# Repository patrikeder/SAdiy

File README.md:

# SAdiy: DIY swept spectrum analyzer

A swept low-IF spectrum analyzer built from ready-made RF modules and controlled by a BeagleBone Black (BBB). The software runs on a PC today against a simulated RF chain. It has not run on the real hardware yet: see [Status](#status).

The code is Python. C++ or Rust comes in only if a measured time per point demands it (`native/`).

## Signal chain

Planned:

```
RF in -> DC block/ESD -> PE4302 -> 500 MHz LPF -> 30 dB amp -> AD831 mixer -> 10.7 MHz IF filter -> IF amp -> log detector -> ADS1115 -> BBB
                                                                  ^
ADF4351 (LO = RF + 10.7 MHz) -> LPF + pad -----------------------+
```

Built so far: PE4302, amp, AD831, detector and ADF4351. The missing stages are listed in priority order in [hw/todo-parts.md](hw/todo-parts.md).

- **Range:** 30 to 480 MHz by default (`config/default.toml`). The AD831 LO limit puts the ceiling at about 489 MHz.
- **Image:** the low IF puts an image 21.4 MHz above each RF, so every signal also shows a copy 21.4 MHz lower on the sweep axis. The optional **Image reject** setting (two sweeps per trace with the LO on both sides, lower reading kept) removes it above about 45 MHz at twice the sweep time; tested in the simulator only.
- **ADC:** an ADS1115 on I2C reads the detector. The BBB on-chip AIN0 stays wired as an optional cross-check.

## Quick start (PC, no hardware)

```bash
python3 -m venv .venv && . .venv/bin/activate
pip install -e .[dev,ui]      # ui adds PyQtGraph and PyQt5, only needed for the GUI
pytest
```

On a Raspberry Pi (aarch64) PyPI has no PyQt5 wheel, so use the Debian packages and a venv that can see them:

```bash
sudo apt install python3-pyqt5 python3-pyqtgraph python3-zmq python3-numpy    # python3-pyqt6 works too
python3 -m venv --system-site-packages .venv && . .venv/bin/activate
pip install -e . --no-deps
```

Run the spectrum analyzer GUI. It starts its own simulated hardware, and its Pins tab drives a fake board:

```bash
python -m sadiy.ui.sa_gui --sim
```

Or run the daemon and a terminal client separately:

```bash
python -m sadiy.server.sweepd --sim &      # publishes on tcp 5556, takes commands on tcp 5557
python -m sadiy.ui.cli_client --count 5    # prints the peak of each sweep
python -m sadiy.ui.cli_client --log-level warning   # also what sweepd reports: its history, then live
```

Bring-up helpers that need no hardware:

```bash
python tools/bringup.py pe4302-pattern --db 16 --from-db 15.5   # V1..V6 write order, for a logic analyzer
python tools/bringup.py pll --mhz 110.7                         # divider, INT, FRAC, MOD
```

Run from a project checkout: the config is read from `config/default.toml` next to `src/`.

## On the BBB

Setup is in [deploy/bbb-setup.md](deploy/bbb-setup.md), including first install and updates without internet: `python tools/make_bbb_package.py` builds the package in `dist/`, and `deploy/sadiy-update.sh` updates an existing installation from it. Sweeping on real hardware is not written yet, so for now the daemon runs in bench mode only:

```bash
cd /opt/sadiy && sudo PYTHONPATH=src python3 -m sadiy.server.sweepd --bench-only --config /etc/sadiy/local.toml   # on the BBB
python -m sadiy.ui.sa_gui --host <bbb-ip> --connect   # on the PC
```

The GUI's **Pins** tab then gives wiring tests over the network:

- a clickable drawing of P8 and P9 with the boards, and live pin levels
- raw access to the ADF4351, PE4302 and both ADCs
- check patterns with a preview and CSV export, to compare with a logic analyzer capture

The daemon enforces the safety rules: the attenuator starts at 31.5 dB, RF outputs stay off until the PLL is locked, and all lines return to a safe state if the client disappears. See [docs/gui.md](docs/gui.md).

**Messages from the daemon.** `sweepd` logs at five levels. The default (info) goes to stderr, which is the journal under systemd: `journalctl -u sweepd -f` over ssh. `-v` is debug, `-vv` adds trace (every point and SPI word, ssh only), `-q` is warning; `[log] level` in the config does the same. Errors, warnings, info and debug also reach the GUI, in the Device log on the Advanced tab, with a count of unread problems on the tab. See "Logging" in [docs/architecture.md](docs/architecture.md).

## How it fits together

```
 sweepd (one process, on the BBB)               clients (any number, any host)
 +-----------------------------------+          +---------------------------+
 | sweep engine or bench mode        |   PUB    | sa_gui / cli_client       |
 | lock detect, median, flags, cal   | -------> |  sweeps: dBm + flags      |
 | PE4302 (GPIO) ADF4351 (SPI)       |          |  log: errors, warnings    |
 | ADS1115 (I2C) AIN0 (IIO)          |   REP    | plot, markers, Pins,      |
 | log ring                          | <------- | Device log                |
 +-----------------------------------+          | commands (JSON)           |
        +--> stderr / journald (ssh)             +---------------------------+
```

`sweepd` is the only process that touches the hardware. Clients talk to it over ZeroMQ: sweep frames and log records on port 5556, JSON commands on port 5557. The BBB does the per-point work (lock detect, median of the reads, calibration, flags for points it does not trust); the GUI keeps the trace modes, markers and peak search. Code layers as `hal` -> `drivers` -> `core` -> `server` -> `ui`, and only `hal` touches the OS, so everything above it runs on a PC against fakes and the simulator. Details and the design decisions are in [docs/architecture.md](docs/architecture.md).

## Repository layout

| Path | What |
|---|---|
| `src/sadiy/pinmap.py` | the BBB pin map: nets, GPIO numbers, what each pin may do. Read by the diagram generator, the daemon and the GUI |
| `src/sadiy/hal/` | SPI, GPIO, I2C and ADC abstraction: Linux backends and recording fakes |
| `src/sadiy/drivers/` | PE4302, ADF4351, ADS1115 and on-chip ADC drivers |
| `src/sadiy/core/` | frequency plan, detector model, calibration, sweep engine with lock gating, median and flags (no hardware access) |
| `src/sadiy/server/` | `sweepd` daemon, wire protocol, bench mode |
| `src/sadiy/logs.py` | log levels, the numbered ring buffer the GUI fetches from, repeat folding; standard library only |
| `src/sadiy/ui/` | terminal client and GUI (`sa_gui.py`, `bench_tab.py`); logic without Qt is in `sa_core.py`, `bench_core.py` and `log_core.py`. `qt_client.py` is an old skeleton |
| `src/sadiy/sim.py` | simulated RF chain |
| `src/sadiy/patterns.py` | pin patterns and SPI frames, for logic analyzer comparison |
| `config/` | TOML configuration; values marked VERIFY need checking on the real boards |
| `hw/` | wiring, diagrams, netlist, per-board notes, test points, missing parts, adapter board (KiCad) |
| `docs/` | architecture, bring-up plans, GUI manual, `handoff.md` (starting on another PC) |
| `deploy/` | BBB setup notes, systemd units, install, update and pin mode scripts, example local config |
| `sna/` | second project: a scalar network analyzer reusing the same chain |
| `tools/` | bring-up and calibration helpers, `gen_diagrams.py`, `make_bbb_package.py` |
| `dist/` | BBB packages built by `make_bbb_package.py`; not in git |
| `tests/` | pytest suite, runs on a PC; GUI tests run offscreen and are skipped without the GUI packages |
| `native/` | placeholder for C++ or Rust |

`hw/netlist.md` and `hw/diagrams/` are generated. To change them, edit `src/sadiy/pinmap.py` or `tools/gen_diagrams.py` and run `python tools/gen_diagrams.py`.

## Hardware documentation

| Document | What |
|---|---|
| [hw/wiring-bbb.md](hw/wiring-bbb.md) | BBB wiring, wiring order, power-on checks |
| [hw/netlist.md](hw/netlist.md) | every signal, strap and supply pin |
| [hw/boards/sbc-adapter/README.md](hw/boards/sbc-adapter/README.md) | adapter board that carries the modules on the BBB |
| [hw/as-built.md](hw/as-built.md) | what is really on the bench |
| [docs/bringup.md](docs/bringup.md) | staged bring-up plan with pass criteria |

The adapter board is BBB only: its Raspberry Pi connector was removed. The Raspberry Pi wiring notes and software paths are still in the repo but are no longer developed.

## Status

| Part | State |
|---|---|
| Frequency plan and PLL math, detector model, calibration, auto-ranging | done, tested |
| Sweep engine, `sweepd`, protocol, terminal client, simulator | done, tested against the simulator |
| Per-point lock gating, median of the reads, flags (unlocked, overload, at floor, outlier) | done, tested with fakes and the simulator; thresholds (`max_dbm`, `floor_dbm`, `outlier_db`) not yet checked on the real detector, and the lock line is not read from a real GPIO until `build_hw_engine` exists |
| Image rejection (two sweeps, opposite LO side, lower reading kept) | done, tested against the simulator; the real mixer with a low-side LO is not verified |
| Logging on the BBB (levels, journald, ring, `log` command) and the GUI Device log | done, tested; never run on a real BBB |
| Spectrum analyzer GUI | done, smoke-tested offscreen against the simulator; not yet used with real hardware or on a real display |
| PE4302 driver | done, tested with fakes; weights and polarity not yet confirmed on the module (`pe4302-walk`) |
| ADS1115 driver | done, tested against a register model only; sweeps do not use it yet |
| Bench mode (Pins tab) | done, **tested on the fake backend only**; the Linux backend has never run on a BBB |
| ADF4351 register packing | R0..R5 written and unit-tested for field positions; **not yet checked against the datasheet text or ADI's software** |
| Sweeping on real hardware (`build_hw_engine`) | **not written** |
| GPIO backend | sysfs; moves to libgpiod once the image is fixed |

Unverified on a real BBB: the pin map, pin multiplexing and `config-pin` modes, and the SPI and I2C device numbers.

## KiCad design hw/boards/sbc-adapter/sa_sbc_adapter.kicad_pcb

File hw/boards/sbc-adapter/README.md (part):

# SBC adapter (KiCad project)

One board that lets the **BeagleBone Black** reach the module boards (PE4302, ADF4351, detector, ADS1115). The board sits on the BBB like a cape: P8 and P9 are male pin headers on the **bottom** side, everything else (module headers, jumpers, test points) is on the **top** side.

**Raspberry Pi support was removed (2026-11-01)** to keep the board to one SBC: J3 (2x20 IDC), the 13 RPi-side series resistors (R2, R4 .. R26) and the RPi supply jumpers JP2 / JP4 are gone from the schematic and the board. Every BBB signal keeps its 220 ohm series resistor at the BBB header (R1, R3 .. R25), as source termination and fault-current limit.

The pin map comes from `../../netlist.md` and `../../wiring-bbb.md`. Nothing was remapped.

## Files

| File | Content |
|---|---|
| `sa_sbc_adapter.kicad_sch` | schematic (single sheet, A1), KiCad 8 file format |
| `sa_sbc_adapter.kicad_pro` | minimal project file |
| `sadiy.kicad_sym`, `sym-lib-table` | project symbol library (all symbols are custom, footprints are stock KiCad ones) |
| `gen_schematic.py` | generator of the FIRST (two-SBC) schematic, a record only: **do not run it over the `.kicad_sch`** |
| `check_schematic.py` | standalone connectivity check against the pin map (no KiCad needed) |
| `preview.svg`, `preview.png` | schematic preview drawn by the generator, **not a KiCad render** |
| `sa_sbc_adapter.kicad_pcb` | board, connectors placed to the BBB cape geometry (see "Board placement") |
| `sadiy.pretty/`, `fp-lib-table` | project footprint library: `BBB_Header_2x23_Male_Bottom` |
| `gen_footprints.py` | writes `sadiy.pretty/` and `fp-lib-table` |
| `remove_rpi.py` | removes J3, JP2, JP4 and the RPi-side resistors from the schematic and the board (record of the 2026-11-01 edit, not re-runnable) |
| `route_check.py`, `route_report.py`, `ROUTABILITY.md`, `routability/` | routability feasibility check (see `ROUTABILITY.md`) |
| `place_connectors.py` | (first layout, includes J3) puts J1, J2, J3 and the cape outline / keep-outs (`Dwgs.User`) on the board (re-runnable) |
| `align_components.py` | (first layout, before the hand edits and before J3 was removed) **places every other part on a regular lattice** (rows, columns, one orientation per class), fits the board outline to the parts and writes it on `Edge.Cuts`; deterministic, re-runnable. Run it after `place_connectors.py` |
| `place_components.py` | earlier free-form placement (greedy, net-driven) that was used to find the macro layout; superseded by `align_components.py`, kept for experiments |
| `check_components.py` | (needs J3, so it no longer runs on the current board) checks overlaps, the board outline, the alignment (lattice, orientations, rows) and the signal-integrity distances |
| `check_placement.py` | (needs J3) checks the pad positions in the board file against the cape geometry |
| `placement.svg`, `placement.png` | placement preview of ALL parts, drawn from the placement data (pads, courtyards, ratsnest of the signal nets), **not a KiCad render** |

The `.kicad_pcb` and `.kicad_sch` are yours. KiCad 10 re-saved them and the board has hand-placed parts (test points, some resistors, JP2/JP4/JP6 before they were removed or moved), so none of the placement scripts is re-run any more.

## Status

- The schematic was checked without KiCad: nets built from wires, labels and pin positions. After the RPi removal: every remaining pin keeps its net, no wire end dangles, no RPI_* label is left.
- **Not yet checked in KiCad.** Run ERC and DRC and pass the output back. Then use "Update PCB from Schematic" once to confirm that schematic and board agree (they were edited in the same way).

## Signal map

| Net | BBB | Module |
|---|---|---|
| SYN_CLK | P9.22 | J6 pin 7 (ADF4351 CLK) |
| SYN_DATA | P9.18 | J6 pin 6 (DAT) |
| SYN_LE | P9.17 | J6 pin 5 (LE) |
| SYN_LD | P9.23 | J6 pin 9 (LD), SBC input |
| SYN_CE | P9.27 | J12 pin 3, jumper to J6 pin 3 (CE) |
| ATT_V1..V6 | P8.7, 8, 9, 10, 11, 12 | J4 pins 2..7 (PE4302 V1..V6) |
| I2C_SDA / I2C_SCL | P9.20 / P9.19 (I2C2) | J10 pins 4 / 3 (ADS1115) |
| detector | P9.39 AIN0, P9.34 GNDA_ADC, P9.32 VDD_ADC (clamp only) | divider from J8 |

## Jumpers and options

| Part | Setting |
|---|---|
| JP1 | 5 V rail joins the BBB VDD_5V (P9.5/6). Case A: external 5 V on J11 powers the BBB, fit JP1 and do not plug the BBB's own supply. Case B: the BBB powers the modules, fit JP1 and leave J11 empty. A BBB powered over USB only has no VDD_5V. |
| JP3 | 3.3 V rail from the BBB (P9.3/4). |
| J12 | ADF4351 CE: jumper 1-2 = tied high (default), 2-3 = from the SBC pin. |
| JP5 | ADF4351 PDR tied high. Remove if the board already pulls it up. |
| JP6 | BBB analog path (divider to AIN0). |
| R27..R32 | 2.2k pull-ups on V1..V6, default after boot = 31.5 dB. Remove for 0 dB. |
| R38 (0R) | joins AGND to GND at one point. |
| 4.7k on I2C | not fitted (DNP). The BBB I2C2 already has pull-ups. |

## Parts (from the schematic)

25 resistors (13 x 220R series, 6 x 2.2k, 2 x 1k, 1 x 3.01k, 1 x 0R, 2 x 4.7k DNP), 10 capacitors (4 x 10u 0805, 6 x 100n 0603), 3 ferrite beads (0805, 2 A), 1 resettable fuse (1812, 2 A), 2 x BAT54S (SOT-23), 11 connectors, 4 jumper headers, 23 test points named as in `../../test-points.md` (TP_5V, TP_5V_SYN, TP_3V3_ATT, TP_PE_V1..V6, TP_SYN_*, TP_DET_OUT, TP_ADC_IN, plus grounds and rails). Footprints are assigned, using stock KiCad libraries.

## Decisions that go beyond the repo notes

- 220 ohm series resistors at the BBB header on every signal (source termination). With the 2.2k pull-ups the low level at the PE4302 input is about 0.3 V, well under its threshold.
- BBB divider is 1k over 3.01k (ratio 0.751, 1.9 V in gives about 1.43 V), 100 nF at the tap, BAT54S clamp to GNDA_ADC and VDD_ADC. Put `detector.divider_ratio = 0.751` in `config/default.toml`.
- ADS1115 path: 1k, 100 nF and a BAT54S clamp to 3V3 and ground. The ADS1115 is a **breakout header** (VDD GND SCL SDA ADDR ALRT A0 A1 A2 A3), not a chip on the board.
- The BBB I2C2 drives I2C_SDA / I2C_SCL for the ADS1115.
- Ferrite beads between the BBB rails and the ADF4351 5 V, the detector 5 V and the PE4302 3.3 V.

## Board placement

Cape geometry (BeagleBone cape, from the SparkFun `BEAGLE_BONE_BLACK_CAPE` footprint, which was made from the BBB gerbers), seen from the top, origin at the top-left corner of the 86.36 x 54.61 mm cape outline. The outline is drawn on `Dwgs.User` at (170, 40) on the board, to the right of the other parts. It is a reference, not the board edge.

| | pin 1 | rows |
|---|---|---|
| P8 (J2) | x = 20.32 mm, y = 4.445 mm | odd pins y = 4.445, even pins y = 1.905 (outer row, top edge) |
| P9 (J1) | x = 20.32 mm, y = 52.705 mm | odd pins y = 52.705 (outer row, bottom edge), even pins y = 50.165 |

Both headers: pin 1 at the Ethernet (left) end, 23 pins per row, 2.54 mm pitch, even pins above odd pins. The two headers are 48.26 mm apart.

- **J1, J2** are on the bottom side with the custom footprint `sadiy:BBB_Header_2x23_Male_Bottom`. The stock 2x23 header cannot be used there: KiCad mirrors a footprint when it moves to the bottom, which gives the wrong pad pattern for P8/P9. The custom footprint is the mirror image, so after KiCad flips it the pads sit exactly on the BBB pattern. Pin 1 is the footprint origin; keep the orientation at 0 and the side at B.Cu. It has no 3D model.
- Also drawn on `Dwgs.User`: the Ethernet connector keep-out, the top-left cut and the three rounded corners of the cape (from the same SparkFun footprint). The reference outline is only for orientation: the board is larger than the cape (see "Component placement"). Not placed: the four BBB mounting holes.
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
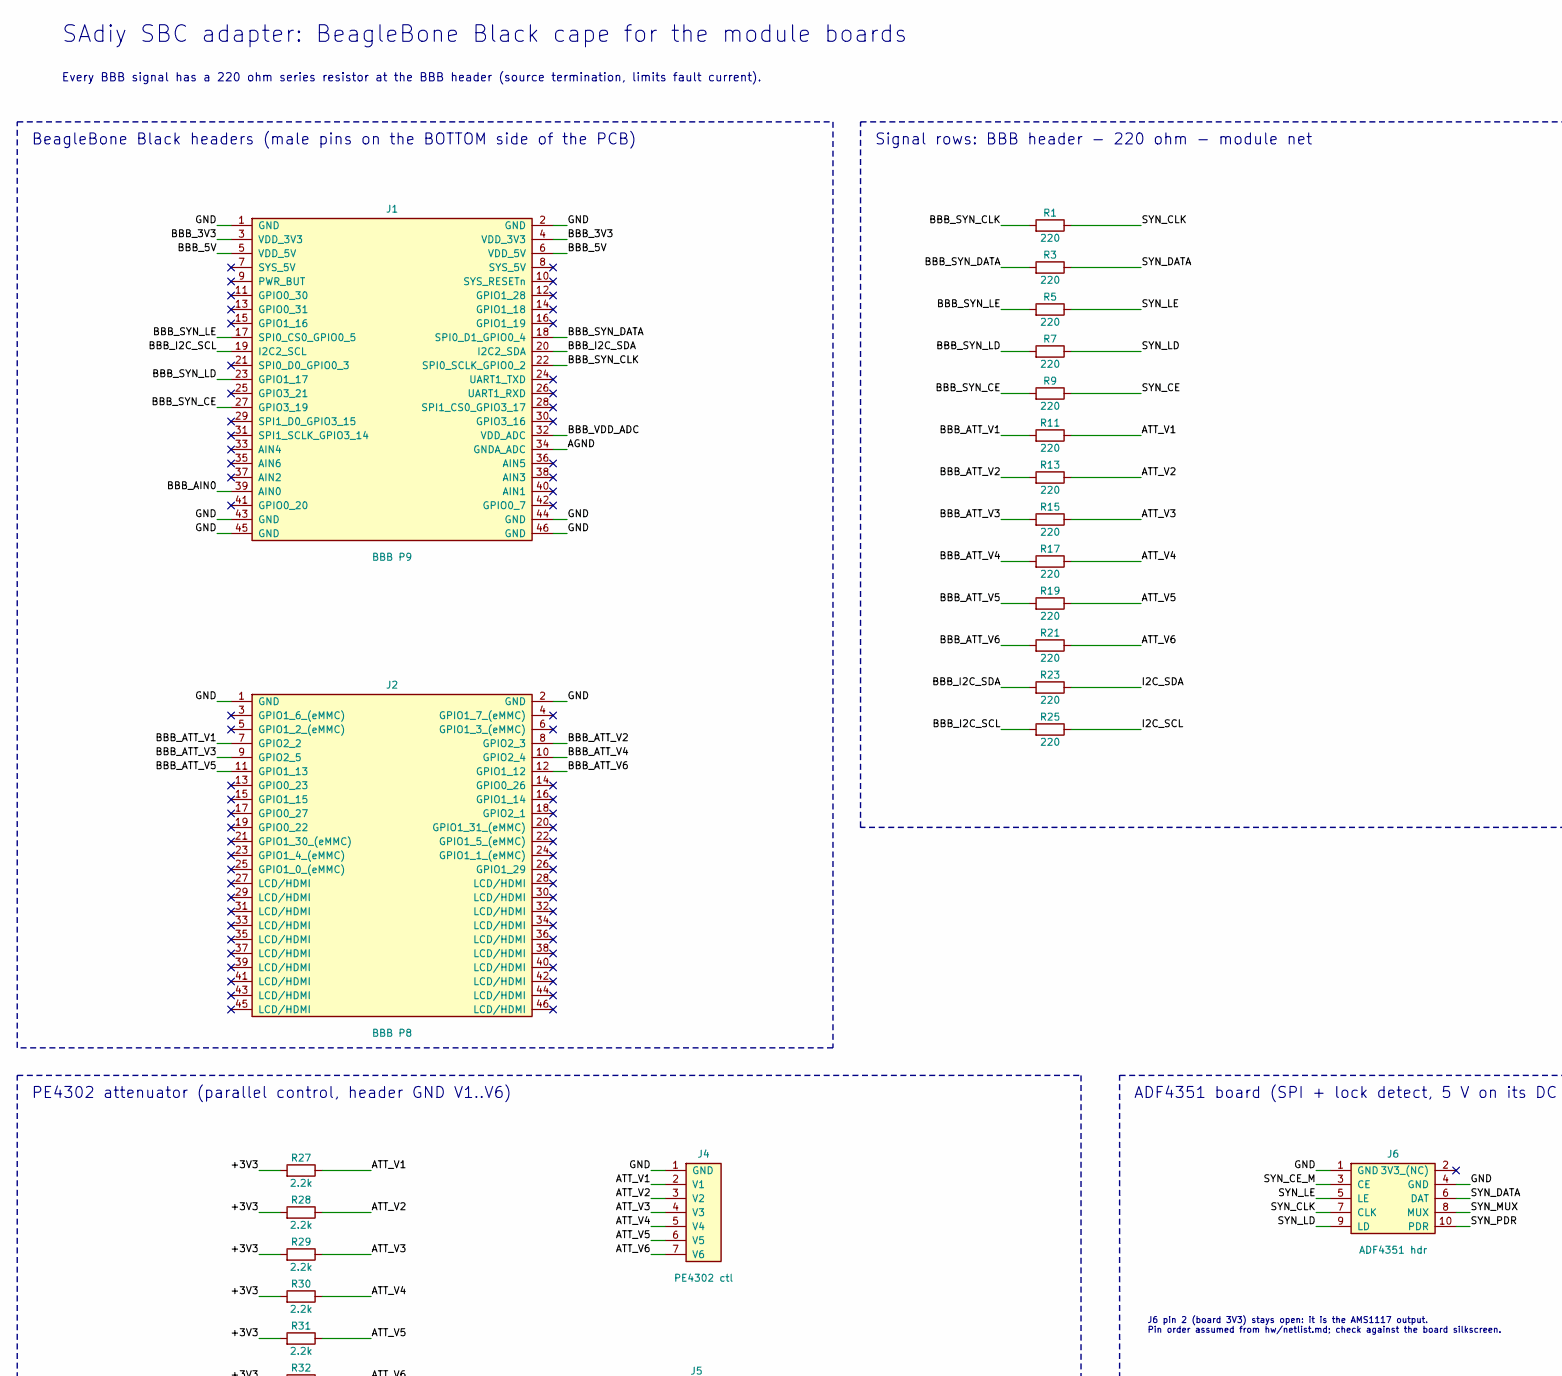
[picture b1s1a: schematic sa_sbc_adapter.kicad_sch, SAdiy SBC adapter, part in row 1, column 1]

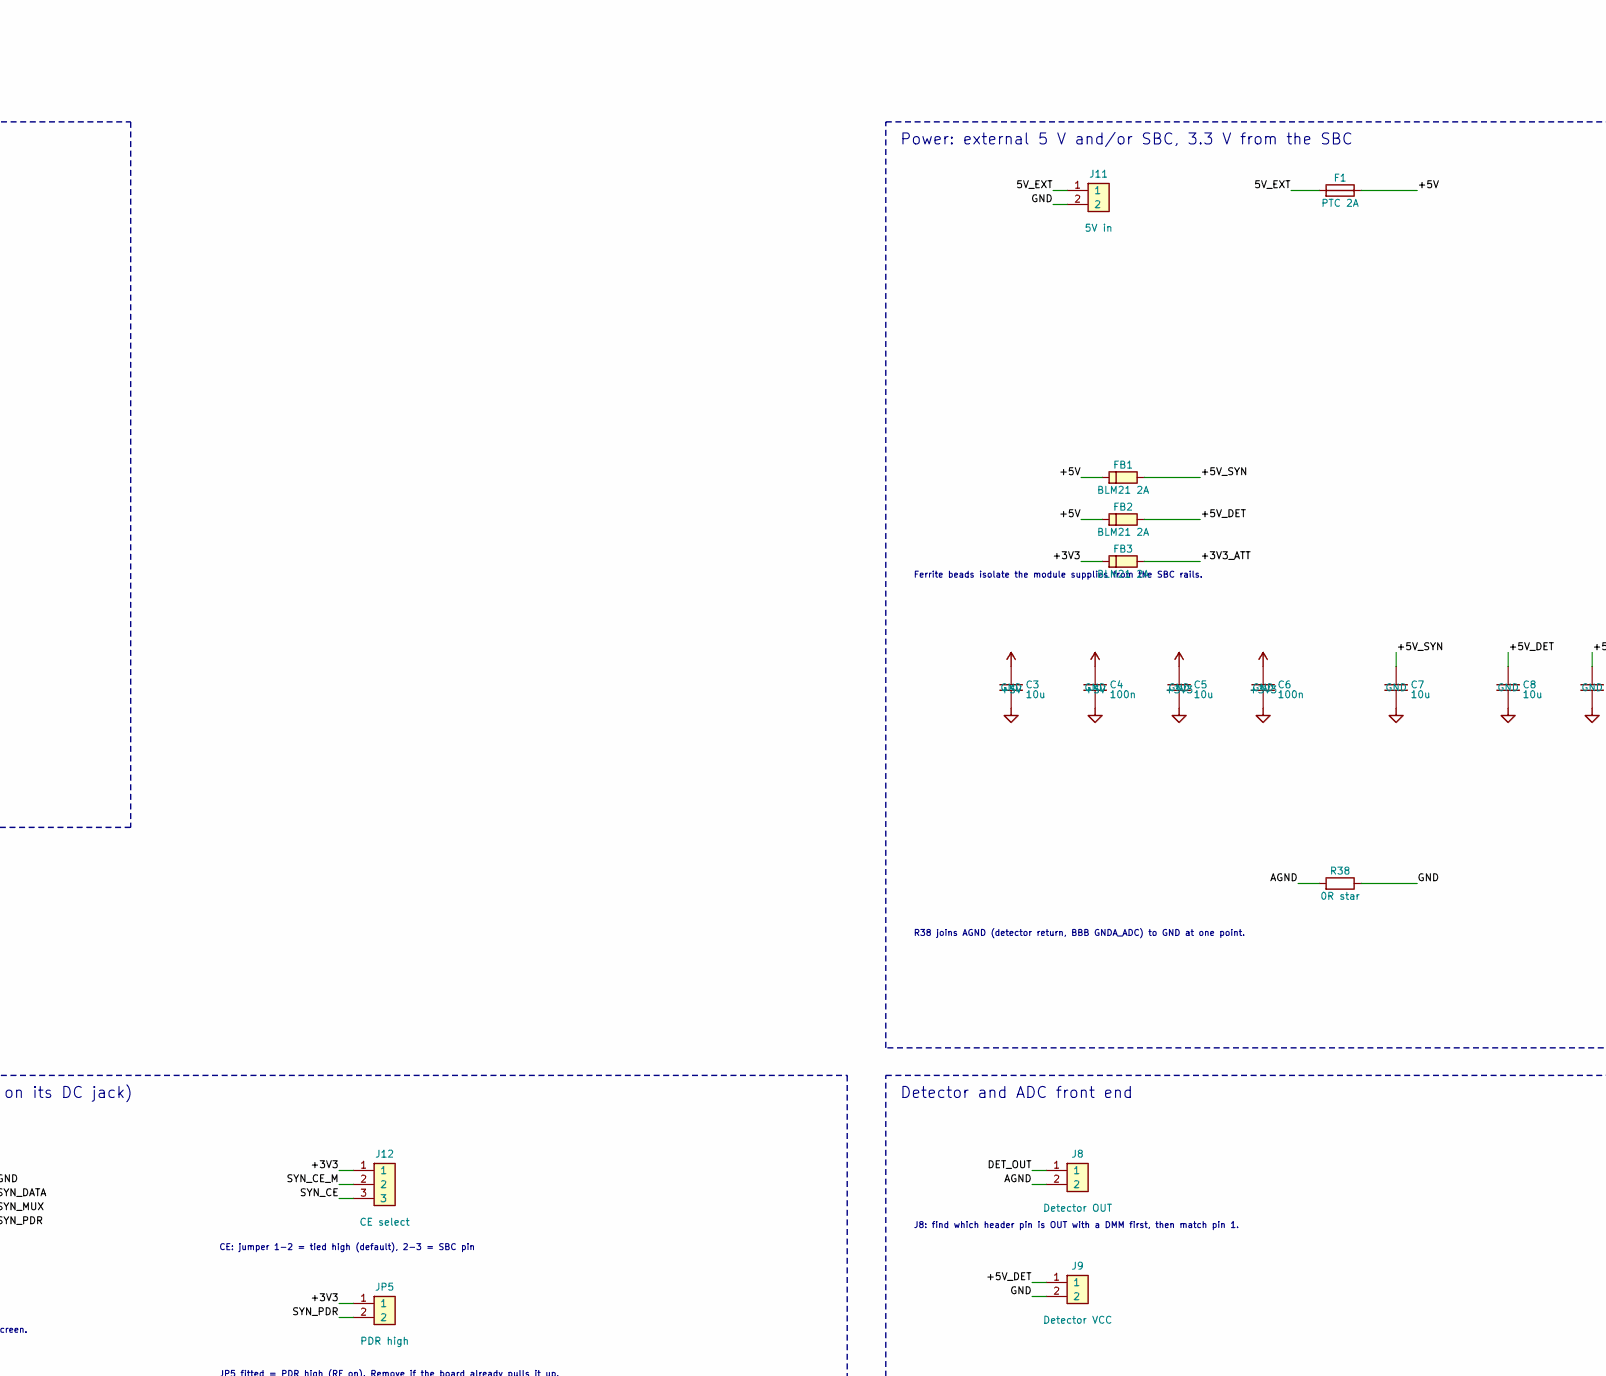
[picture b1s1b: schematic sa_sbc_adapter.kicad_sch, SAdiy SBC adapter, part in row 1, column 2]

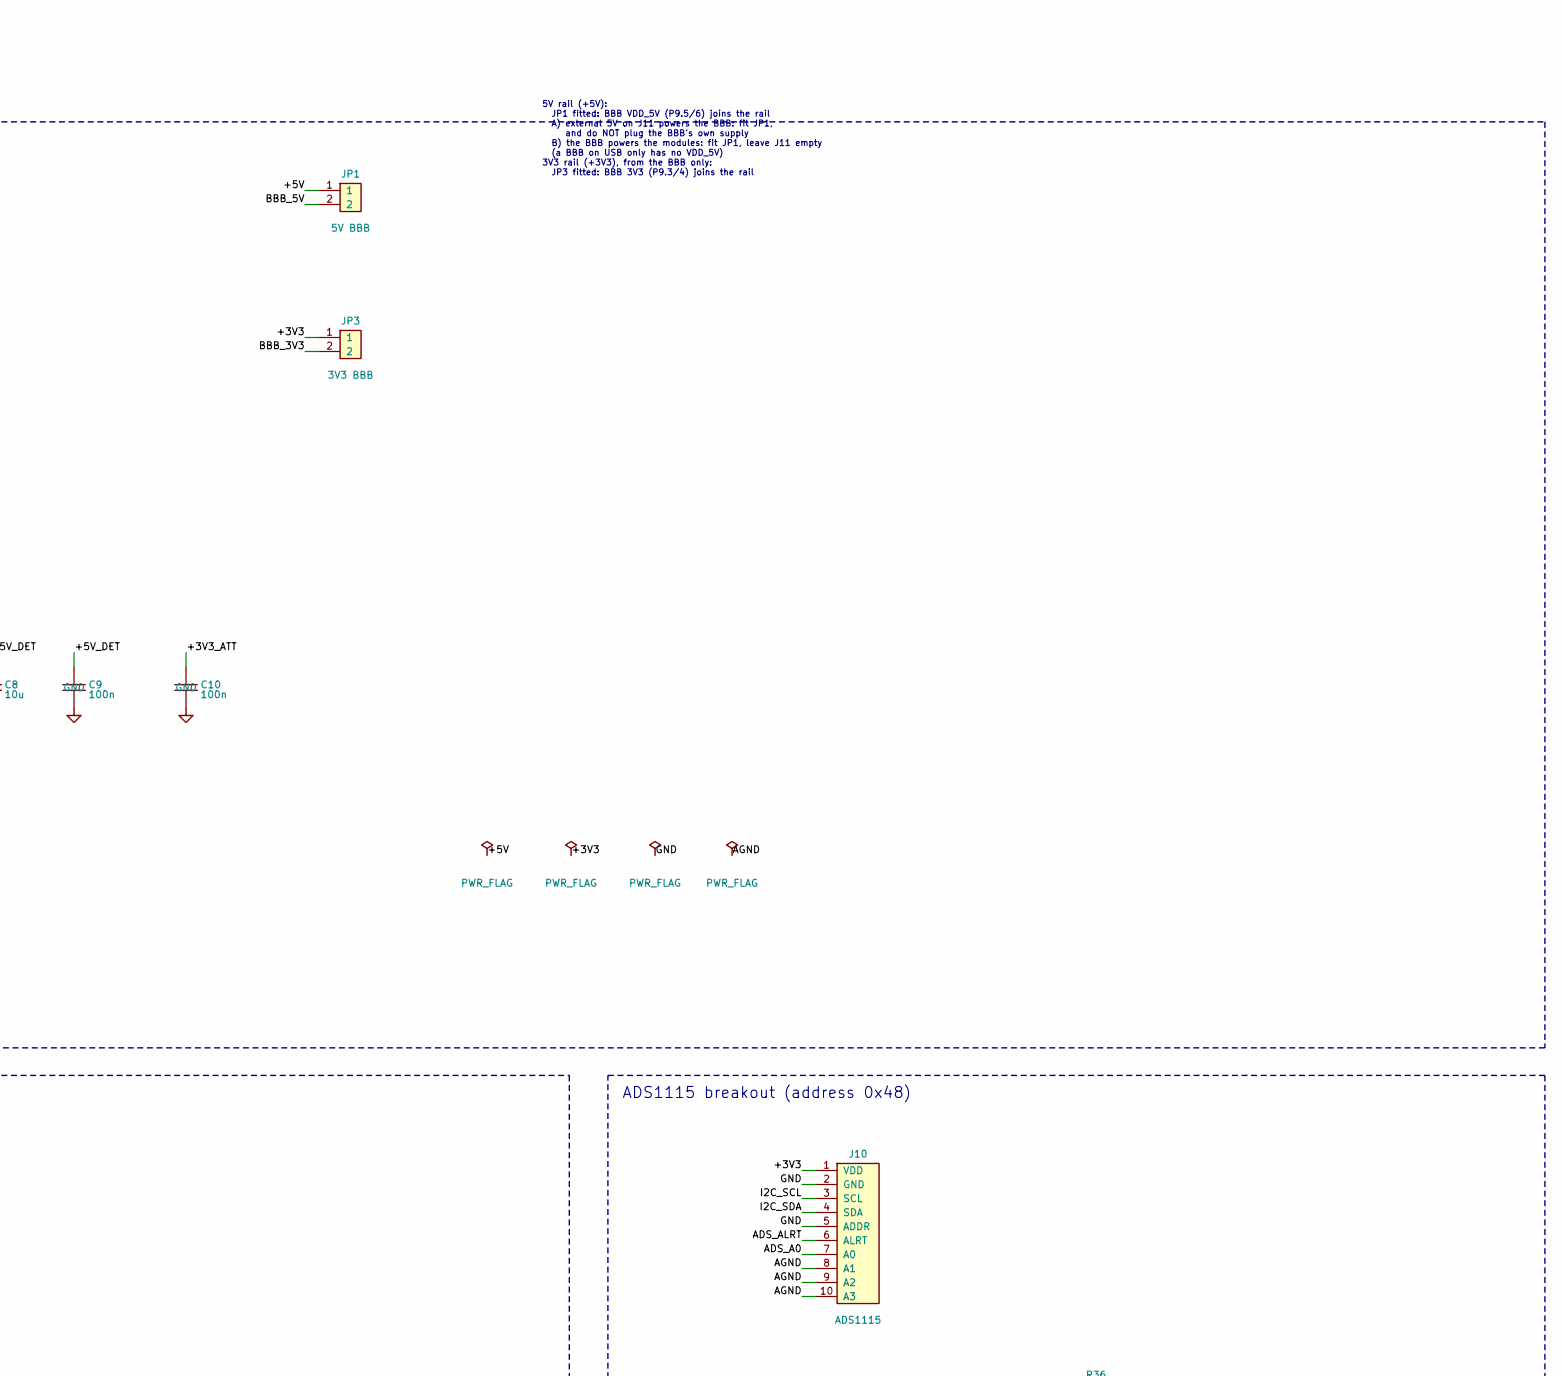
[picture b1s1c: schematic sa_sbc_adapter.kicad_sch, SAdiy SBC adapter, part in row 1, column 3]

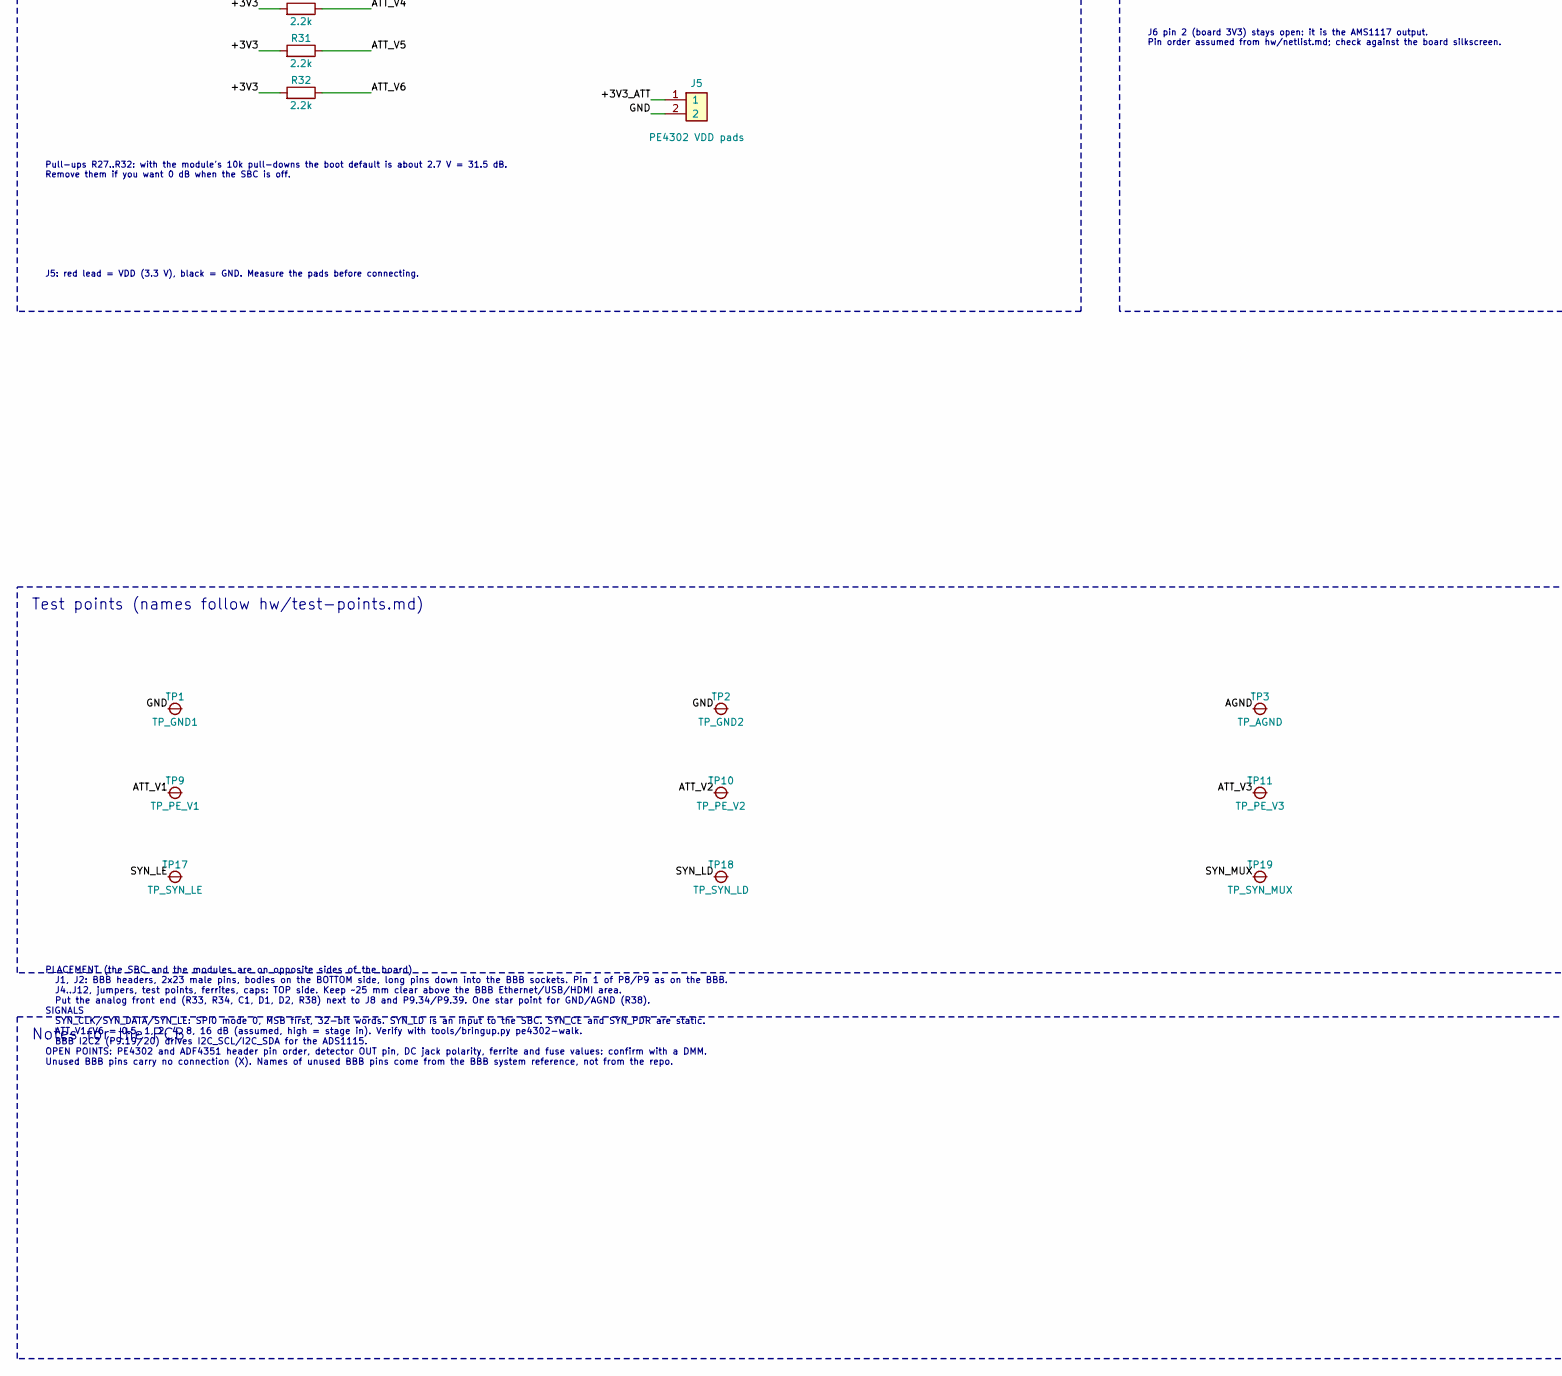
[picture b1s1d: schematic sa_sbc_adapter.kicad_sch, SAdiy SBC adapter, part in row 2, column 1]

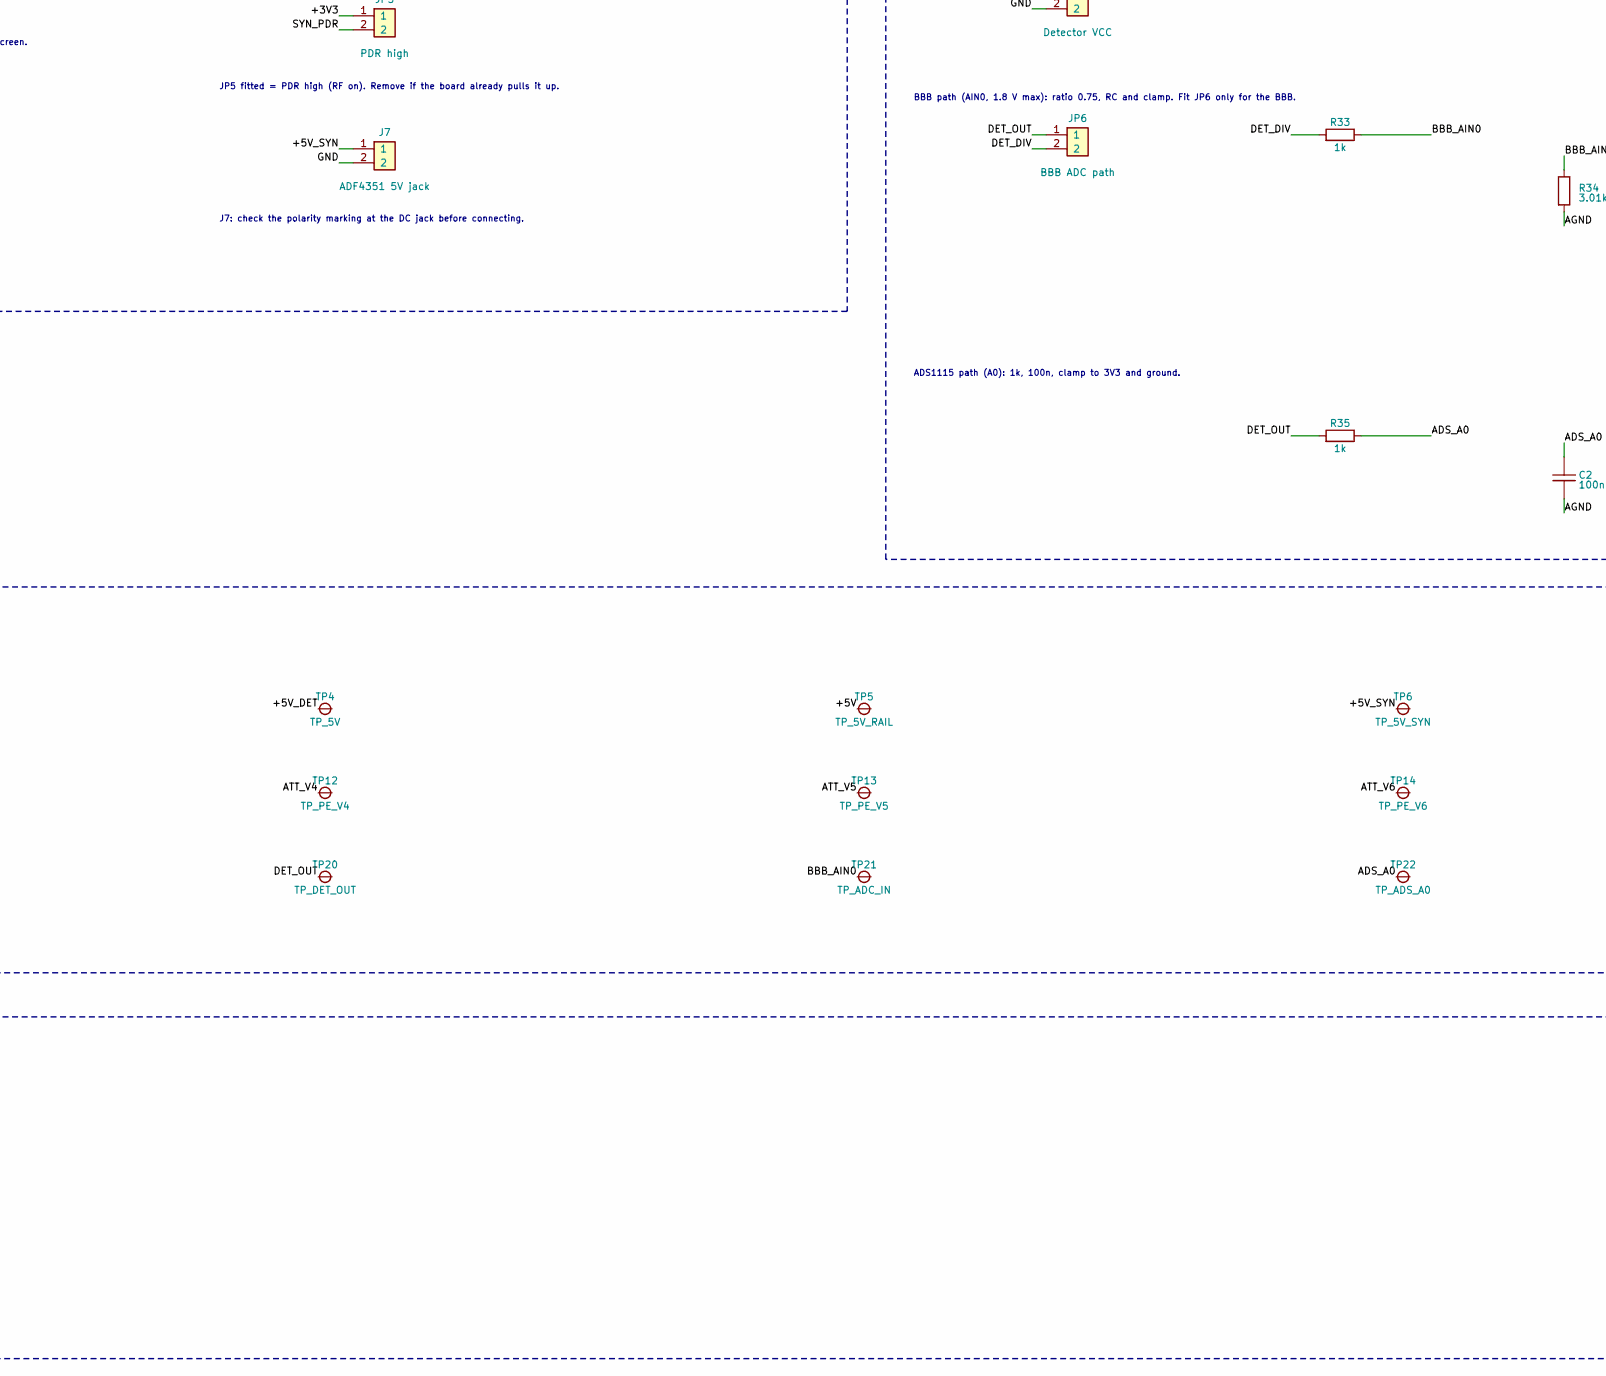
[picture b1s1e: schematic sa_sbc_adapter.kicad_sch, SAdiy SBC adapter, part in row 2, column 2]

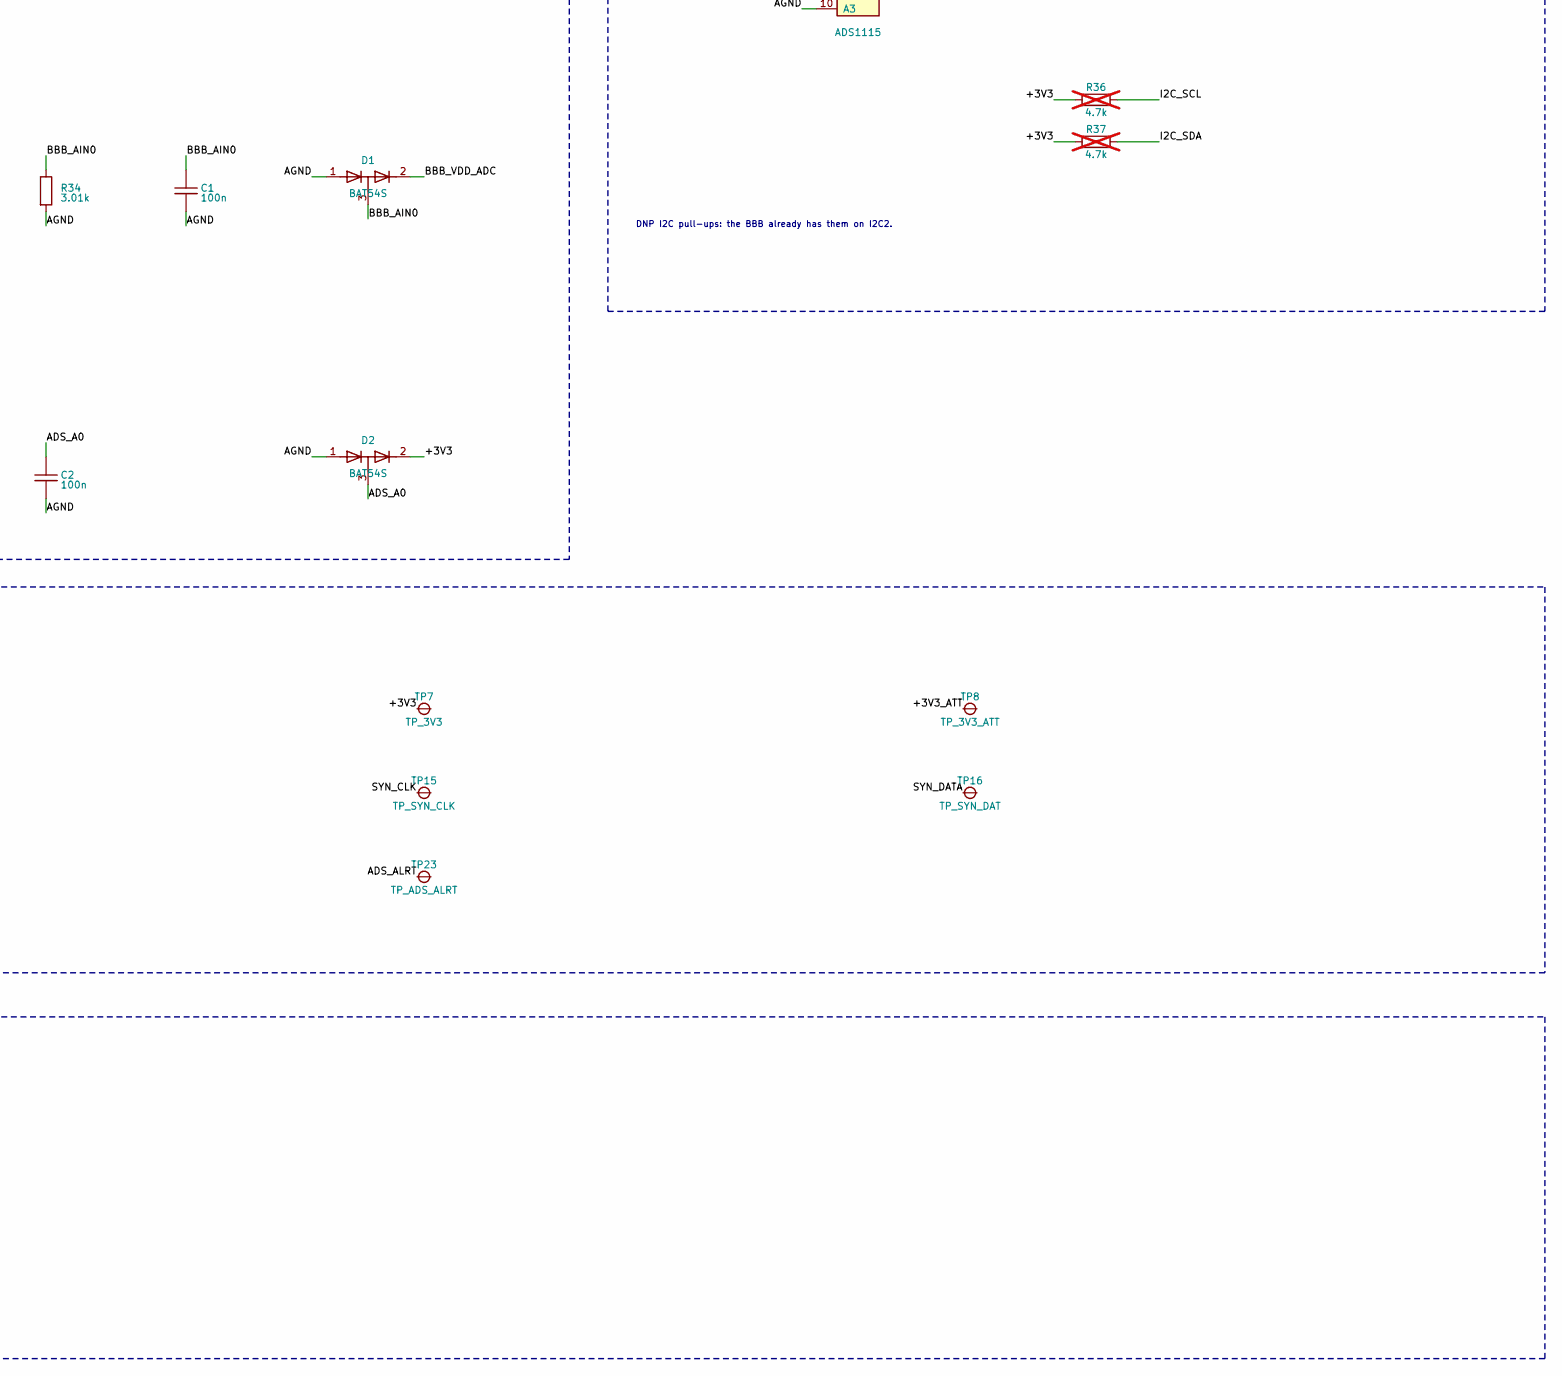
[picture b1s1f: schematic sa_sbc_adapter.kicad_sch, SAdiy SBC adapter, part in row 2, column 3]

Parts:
C1, C2, C4, C6, C9, C10: 100n; C_0603_1608Metric
C3, C5, C7, C8: 10u; C_0805_2012Metric
D1, D2: BAT54S; SOT-23
F1: PTC 2A; Fuse_1812_4532Metric
FB1, FB2, FB3: BLM21 2A; L_0805_2012Metric
J1: BBB P9; BBB_Header_2x23_Male_Bottom
J2: BBB P8; BBB_Header_2x23_Male_Bottom
J4: PE4302 ctl; PinHeader_1x07_P2.54mm_Vertical
J5: PE4302 VDD pads; PinHeader_1x02_P2.54mm_Vertical
J6: ADF4351 hdr; PinHeader_2x05_P2.54mm_Vertical
J7: ADF4351 5V jack; PinHeader_1x02_P2.54mm_Vertical
J8: Detector OUT; PinHeader_1x02_P2.54mm_Vertical
J9: Detector VCC; PinHeader_1x02_P2.54mm_Vertical
J10: ADS1115; PinHeader_1x10_P2.54mm_Vertical
J11: 5V in; PinHeader_1x02_P2.54mm_Vertical
J12: CE select; PinHeader_1x03_P2.54mm_Vertical
JP1: 5V BBB; PinHeader_1x02_P2.54mm_Vertical
JP3: 3V3 BBB; PinHeader_1x02_P2.54mm_Vertical
JP5: PDR high; PinHeader_1x02_P2.54mm_Vertical
JP6: BBB ADC path; PinHeader_1x02_P2.54mm_Vertical
R1, R3, R5, R7, R9, R11, R13, R15, R17, R19, R21, R23, R25: 220; R_0603_1608Metric
R27, R28, R29, R30, R31, R32: 2.2k; R_0603_1608Metric
R33, R35: 1k; R_0603_1608Metric
R34: 3.01k; R_0603_1608Metric
R36, R37: 4.7k; R_0603_1608Metric; not fitted
R38: 0R star; R_0603_1608Metric
TP1: TP_GND1; TestPoint_Pad_D1.5mm
TP2: TP_GND2; TestPoint_Pad_D1.5mm
TP3: TP_AGND; TestPoint_Pad_D1.5mm
TP4: TP_5V; TestPoint_Pad_D1.5mm
TP5: TP_5V_RAIL; TestPoint_Pad_D1.5mm
TP6: TP_5V_SYN; TestPoint_Pad_D1.5mm
TP7: TP_3V3; TestPoint_Pad_D1.5mm
TP8: TP_3V3_ATT; TestPoint_Pad_D1.5mm
TP9: TP_PE_V1; TestPoint_Pad_D1.5mm
TP10: TP_PE_V2; TestPoint_Pad_D1.5mm
TP11: TP_PE_V3; TestPoint_Pad_D1.5mm
TP12: TP_PE_V4; TestPoint_Pad_D1.5mm
TP13: TP_PE_V5; TestPoint_Pad_D1.5mm
TP14: TP_PE_V6; TestPoint_Pad_D1.5mm
TP15: TP_SYN_CLK; TestPoint_Pad_D1.5mm
TP16: TP_SYN_DAT; TestPoint_Pad_D1.5mm
TP17: TP_SYN_LE; TestPoint_Pad_D1.5mm
TP18: TP_SYN_LD; TestPoint_Pad_D1.5mm
TP19: TP_SYN_MUX; TestPoint_Pad_D1.5mm
TP20: TP_DET_OUT; TestPoint_Pad_D1.5mm
TP21: TP_ADC_IN; TestPoint_Pad_D1.5mm
TP22: TP_ADS_A0; TestPoint_Pad_D1.5mm
TP23: TP_ADS_ALRT; TestPoint_Pad_D1.5mm

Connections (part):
+3V3: C5.1, C6.1, D2.2 (K2), FB3.1, J10.1 (VDD), J12.1, JP3.1, JP5.1, R27.1, R28.1, R29.1, R30.1, R31.1, R32.1, R36.1, R37.1, TP7.1 (1_1)
+5V: C3.1, C4.1, F1.2, FB1.1, FB2.1, JP1.1, TP5.1 (1_1)
/5V_EXT: F1.1, J11.1
/+3V3_ATT: C10.1, FB3.2, J5.1, TP8.1 (1_1)
/+5V_DET: C8.1, C9.1, FB2.2, J9.1, TP4.1 (1_1)
/+5V_SYN: C7.1, FB1.2, J7.1, TP6.1 (1_1)
/ADS_A0: C2.1, D2.3 (K1/A2), J10.7 (A0), R35.2, TP22.1 (1_1)
/ADS_ALRT: J10.6 (ALRT), TP23.1 (1_1)
/AGND: C1.2, C2.2, D1.1 (A1), D2.1 (A1), J1.34 (GNDA_ADC), J8.2, J10.8 (A1), J10.9 (A2), J10.10 (A3), R34.2, R38.1, TP3.1 (1_1)
/ATT_V1: J4.2 (V1), R11.2, R27.2, TP9.1 (1_1)
/ATT_V2: J4.3 (V2), R13.2, R28.2, TP10.1 (1_1)
/ATT_V3: J4.4 (V3), R15.2, R29.2, TP11.1 (1_1)
/ATT_V4: J4.5 (V4), R17.2, R30.2, TP12.1 (1_1)
/ATT_V5: J4.6 (V5), R19.2, R31.2, TP13.1 (1_1)
/ATT_V6: J4.7 (V6), R21.2, R32.2, TP14.1 (1_1)
/BBB_3V3: J1.3 (VDD_3V3), J1.4 (VDD_3V3), JP3.2
/BBB_5V: J1.5 (VDD_5V), J1.6 (VDD_5V), JP1.2
/BBB_AIN0: C1.1, D1.3 (K1/A2), J1.39 (AIN0), R33.2, R34.1, TP21.1 (1_1)
/BBB_ATT_V1: J2.7 (GPIO2_2), R11.1
/BBB_ATT_V2: J2.8 (GPIO2_3), R13.1
/BBB_ATT_V3: J2.9 (GPIO2_5), R15.1
/BBB_ATT_V4: J2.10 (GPIO2_4), R17.1
/BBB_ATT_V5: J2.11 (GPIO1_13), R19.1
/BBB_ATT_V6: J2.12 (GPIO1_12), R21.1
/BBB_I2C_SCL: J1.19 (I2C2_SCL), R25.1
/BBB_I2C_SDA: J1.20 (I2C2_SDA), R23.1
/BBB_SYN_CE: J1.27 (GPIO3_19), R9.1
/BBB_SYN_CLK: J1.22 (SPI0_SCLK_GPIO0_2), R1.1
/BBB_SYN_DATA: J1.18 (SPI0_D1_GPIO0_4), R3.1
/BBB_SYN_LD: J1.23 (GPIO1_17), R7.1
/BBB_SYN_LE: J1.17 (SPI0_CS0_GPIO0_5), R5.1
/BBB_VDD_ADC: D1.2 (K2), J1.32 (VDD_ADC)
/DET_DIV: JP6.2, R33.1
/DET_OUT: J8.1, JP6.1, R35.1, TP20.1 (1_1)
/I2C_SCL: J10.3 (SCL), R25.2, R36.2
/I2C_SDA: J10.4 (SDA), R23.2, R37.2
/SYN_CE: J12.3, R9.2
/SYN_CE_M: J6.3 (CE), J12.2
/SYN_CLK: J6.7 (CLK), R1.2, TP15.1 (1_1)
/SYN_DATA: J6.6 (DAT), R3.2, TP16.1 (1_1)
/SYN_LD: J6.9 (LD), R7.2, TP18.1 (1_1)
/SYN_LE: J6.5 (LE), R5.2, TP17.1 (1_1)
/SYN_MUX: J6.8 (MUX), TP19.1 (1_1)
/SYN_PDR: J6.10 (PDR), JP5.2
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
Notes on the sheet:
J6 pin 2 (board 3V3) stays open: it is the AMS1117 output. Pin order assumed from hw/netlist.md; check against the board silkscreen.
Detector and ADC front end
5V rail (+5V): JP1 fitted: BBB VDD_5V (P9.5/6) joins the rail A) external 5V on J11 powers the BBB: fit JP1, and do NOT plug the BBB's own supply B) the BBB powers the modules: fit JP1, leave J11 empty (a BBB on USB only has no VDD_5V) 3V3 rail (+3V3), from the BBB only: JP3 fitted: BBB 3V3 (P9.3/4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
ADS1115 path (A0): 1k, 100n, clamp to 3V3 and ground.
Power: external 5 V and/or SBC, 3.3 V from the SBC
SAdiy SBC adapter: BeagleBone Black cape for the module boards
ADS1115 breakout (address 0x48)
R38 joins AGND (detector return, BBB GNDA_ADC) to GND at one point.
Test points (names follow hw/test-points.md)
DNP I2C pull-ups: the BBB already has them on I2C2.
ADF4351 board (SPI + lock detect, 5 V on its DC jack)
CE: jumper 1-2 = tied high (default), 2-3 = SBC pin
J8: find which header pin is OUT with a DMM first, then match pin 1.
PE4302 attenuator (parallel control, header GND V1..V6)
Every BBB signal has a 220 ohm series resistor at the BBB header (source termination, limits fault current).
Notes for the PCB
Signal rows: BBB header - 220 ohm - module net
J7: check the polarity marking at the DC jack before connecting.
J5: red lead = VDD (3.3 V), black = GND. Measure the pads before connecting.
BeagleBone Black headers (male pins on the BOTTOM side of the PCB)
Pull-ups R27..R32: with the module's 10k pull-downs the boot default is about 2.7 V = 31.5 dB. Remove them if you want 0 dB when the SBC is off.
BBB path (AIN0, 1.8 V max): ratio 0.75, RC and clamp. Fit JP6 only for the BBB.
PLACEMENT (the SBC and the modules are on opposite sides of the board) J1, J2: BBB headers, 2x23 male pins, bodies on the BOTTOM side, long pins down into the BBB sockets. Pin 1 of P8/P9 as on the BBB. J4..J12, jumpers, test points, ferrites, caps: TOP side. Keep ~25 mm clear above the BBB Ethernet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
Ferrite beads isolate the module supplies from the SBC rails.
JP5 fitted = PDR high (RF on). Remove if the board already pulls it up.

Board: 2 copper layers, 79 parts (2 on the bottom side), 45 nets, no tracks yet.

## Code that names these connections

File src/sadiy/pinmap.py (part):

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# One entry per SBC-to-board signal. bbb is a P9 pin number or a string like "P8.7"; rpi is the physical
# pin (None = not used there). mux is the `config-pin` mode of a bus pin, restored when it stops being a GPIO.
NETS = [
    dict(id="SYN_CLK", dev="ADF4351", dpin="CLK", kind="spi", dir="SBC to board", bbb=22, rpi=23, mux="spi_sclk",
         note="SPI mode 0, MSB first"),
    dict(id="SYN_DATA", dev="ADF4351", dpin="DAT", kind="spi", dir="SBC to board", bbb=18, rpi=19, mux="spi",
         note="32-bit words"),
    dict(id="SYN_LE", dev="ADF4351", dpin="LE", kind="spi", dir="SBC to board", bbb=17, rpi=24, mux="spi_cs",
         note="SPI0 CS0, which is /dev/spidevN.0 (N = bus number, spi_device = 0); used as SPI chip select; data latches on the rising edge at the end of a transfer"),
    dict(id="SYN_LD", dev="ADF4351", dpin="LD", kind="gpio", dir="board to SBC", bbb=23, rpi=35,
         note="digital lock detect output (Lock_Flag LED on the board), GPIO input; the MUX pin stays unused"),
    dict(id="SYN_CE", dev="ADF4351", dpin="CE", kind="reserved", dir="SBC to board", bbb=27, rpi=36,
         note="optional; tie the CE header pin to 3V3 until needed"),
    dict(id="ATT_V1", dev="PE4302", dpin="V1 (0.5 dB)", kind="gpio", dir="SBC to board", bbb="P8.7", rpi=29,
         note="assumed weight; verify order and polarity with pe4302-walk"),
    dict(id="ATT_V2", dev="PE4302", dpin="V2 (1 dB)", kind="gpio", dir="SBC to board", bbb="P8.8", rpi=31,
         note="assumed 1 dB stage"),
    dict(id="ATT_V3", dev="PE4302", dpin="V3 (2 dB)", kind="gpio", dir="SBC to board", bbb="P8.9", rpi=32,
         note="assumed 2 dB stage"),
    dict(id="ATT_V4", dev="PE4302", dpin="V4 (4 dB)", kind="gpio", dir="SBC to board", bbb="P8.10", rpi=33,
         note="assumed 4 dB stage"),
    dict(id="ATT_V5", dev="PE4302", dpin="V5 (8 dB)", kind="gpio", dir="SBC to board", bbb="P8.11", rpi=38,
         note="assumed 8 dB stage"),
    dict(id="ATT_V6", dev="PE4302", dpin="V6 (16 dB)", kind="gpio", dir="SBC to board", bbb="P8.12", rpi=40,
         note="assumed 16 dB stage"),
    dict(id="DET_ADC", dev="Detector", dpin="VOUT via divider", kind="analog", dir="board to SBC", bbb=39,
         rpi=None, note="BBB: AIN0 through the divider, a cross-check only (the ADS1115 is the main ADC); 0 to 1.8 V absolute maximum. RPi: ADS1115 only"),
    dict(id="ADC_GND", dev="Detector", dpin="GND", kind="gnd", dir="return", bbb=34, rpi=None,
         note="optional, AIN0 cross-check only"),
    dict(id="I2C_SDA", dev="ADS1115", dpin="SDA", kind="i2c", dir="bidirectional", bbb=20, rpi=3, mux="i2c",
         note="main ADC on both platforms. BBB: I2C2 on the adapter board, which already has pull-ups (4.7k on the adapter not fitted)"),
    dict(id="I2C_SCL", dev="ADS1115", dpin="SCL", kind="i2c", dir="SBC to board", bbb=19, rpi=5, mux="i2c",
         note="main ADC on both platforms. BBB: I2C2 on the adapter board"),
]

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

def find(name: str) -> Pin:
    """Look a pin up by id ("P8.7") or by net ("ATT_V1"). KeyError when there is no such pin."""
    pin = PINS.get(name) or BY_NET.get(name)
    if pin is None:
        raise KeyError(f"no pin or net called {name!r}")
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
